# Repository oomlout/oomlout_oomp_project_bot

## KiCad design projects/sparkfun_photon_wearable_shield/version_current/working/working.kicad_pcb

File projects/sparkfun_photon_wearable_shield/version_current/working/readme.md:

# OOMP Project  
## Photon_Wearable_Shield  by sparkfun  
  
oomp key: oomp_projects_flat_sparkfun_photon_wearable_shield  
(snippet of original readme)  
  
SparkFun Photon Wearable Shield  
  
========================================  

[*SparkFun Photon Wearable Shield (DEV-13328)*](https://www.sparkfun.com/products/13328)  
  
The SparkFun Photon Wearable Shield makes it easy to add the WiFi enabled Photon to any wearables project. Each pin on the Photon is broken out into large sewing pins. Use conductive thread to make your next wearables projects. The large pins are also great for using conductive paint to create any project that needs WiFi. There are even optional smaller pins for soldering flexible wires. The SparkFun Photon Wearable Shield comes with the headers already soldered on, so you can plug and play!  
  
The Particle Photon is a tiny WiFi development kit for creating connected projects and products. Sporting a 120Mhz ARM Cortex M3 and built-in WiFi, the Photon is not only powerful, but easy to use. The small form factor is ideal for IoT projects with cloud-connectivity.  
  
Note: This Photon Wearable Shield does not include a Photon module and is currently available for preorder with a tentative release date of June 2015.  
  
Features:  
  
* 24 Large Sewing Tabs  
* Headers and Connectors Pre-Soldered  
* Compatible with the Photon and the Core  
  
Repository Contents  
-------------------  
  
* **/Production** - Production panel files (.brd)  
* **/Hardware** - Eagle design files (.brd, .sch)  
  
Documentation  
--------------  
* **[SparkFun Photon Wearab  
  full source readme at [readme_src.md](readme_src.md)  
  
source repo at: [https://github.com/sparkfun/Photon_Wearable_Shield](https://github.com/sparkfun/Photon_Wearable_Shield)  
## Board  

## Schematic  

[schematic pdf](working_schematic.pdf)  
## Images

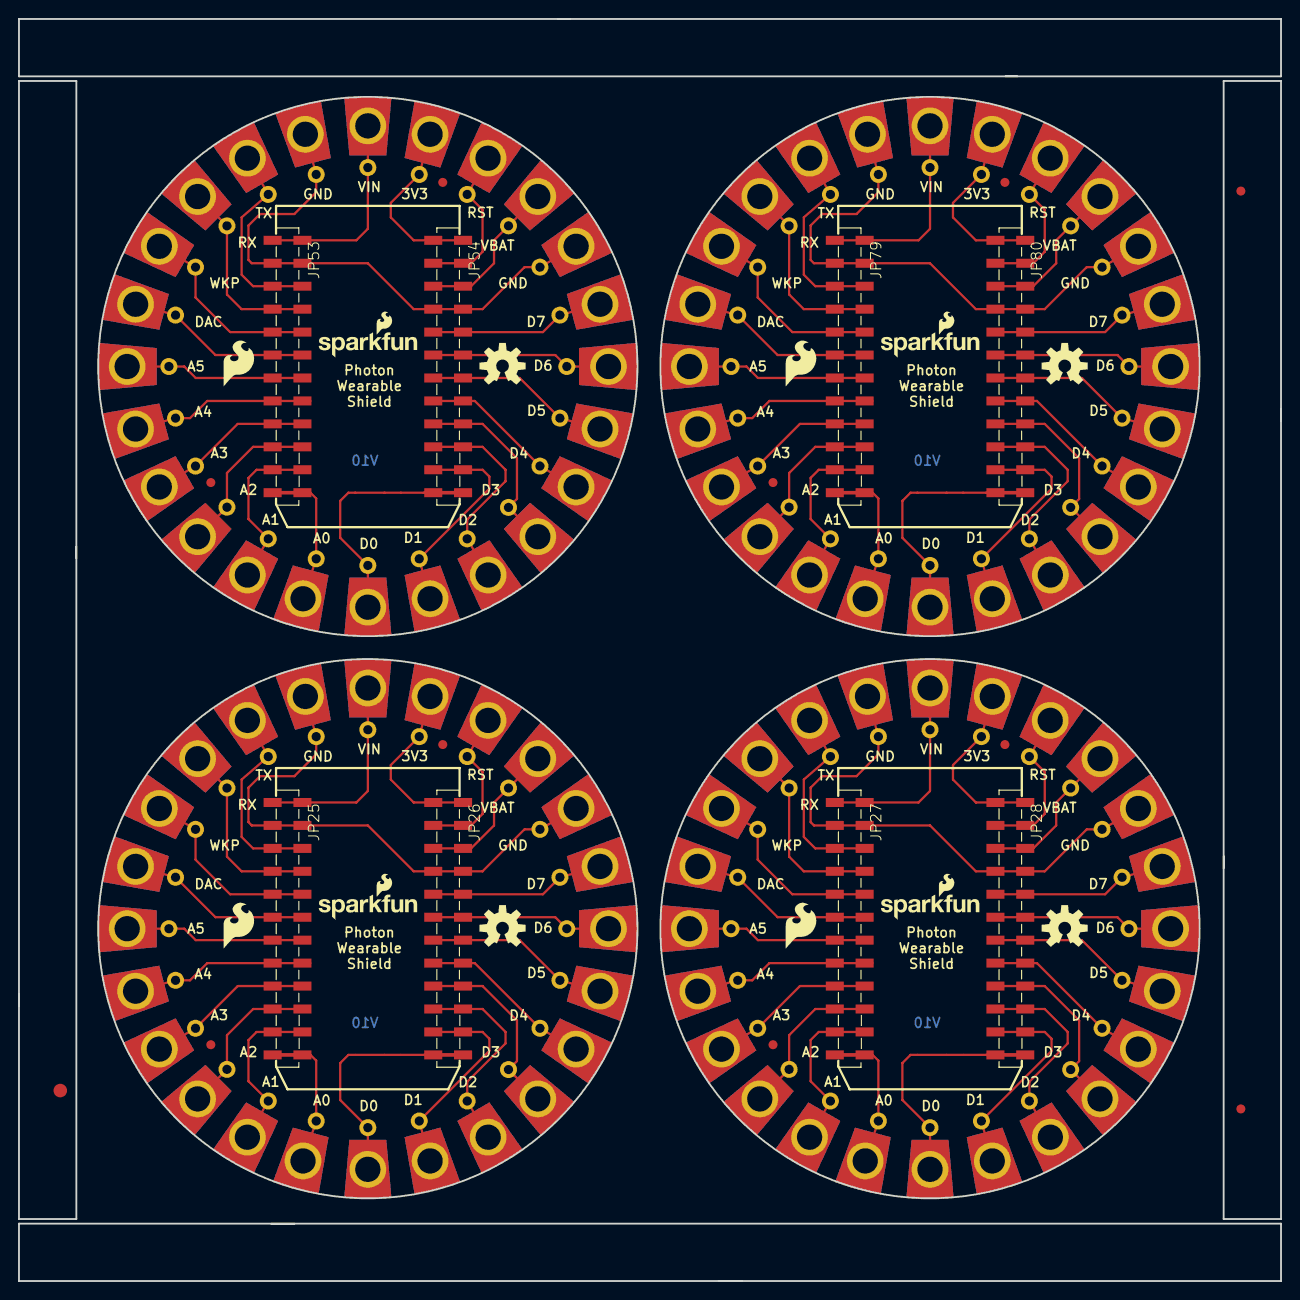
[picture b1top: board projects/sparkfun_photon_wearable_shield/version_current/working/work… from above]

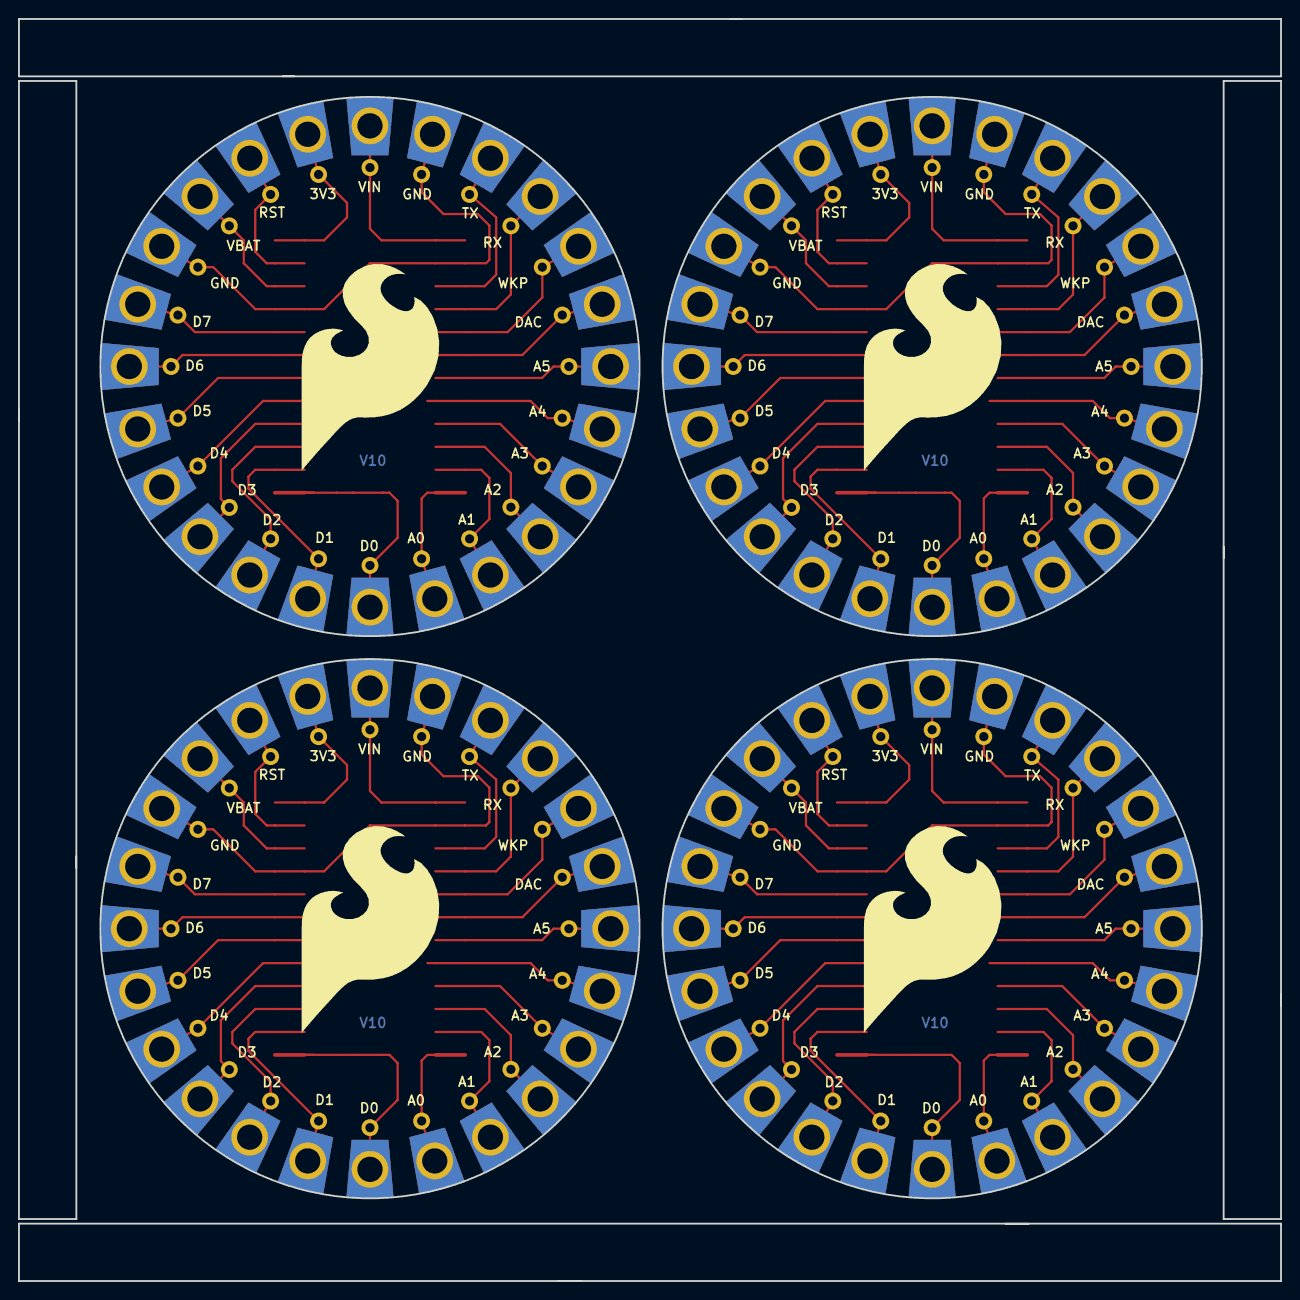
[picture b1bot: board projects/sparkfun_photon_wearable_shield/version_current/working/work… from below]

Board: 2 copper layers, 139.7 x 139.7 mm, 227 parts (4 on the bottom side), 92 nets.

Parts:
E$1: FIDUCIAL-1.5X3
E$4, E$5: FIDUCIAL-1X2
FID1, FID2, FID3, FID4, FID5, FID6, FID7, FID8: FIDUCIAL1X2; FIDUCIAL-1X2
J1, J2, J3, J4, J5, J6, J7, J8, J9, J10, J11, J12, J13, J14, J15, J16, J17, J18, J19, J20, J21, J22, J23, J24, J25, J26, J27, J28, J29, J30, J31, J32, J33, J34, J35, J36, J37, J38, J39, J40, J41, J42, J43, J44, J45, J46, J47, J48, J49, J50, J51, J52, J53, J54, J55, J56, J57, J58, J59, J60, J61, J62, J63, J64, J65, J66, J67, J68, J69, J70, J71, J72, J73, J74, J75, J76, J77, J78, J79, J80, J81, J82, J83, J84, J85, J86, J87, J88, J89, J90, J91, J92, J93, J94, J95, J96: PAD; PAD-LONG-2-SIDED
JP1, JP2, JP3, JP4, JP5, JP6, JP7, JP8, JP9, JP10, JP11, JP12, JP13, JP14, JP15, JP16, JP17, JP18, JP19, JP20, JP21, JP22, JP23, JP24, JP29, JP30, JP31, JP32, JP33, JP34, JP35, JP36, JP37, JP38, JP39, JP40, JP41, JP42, JP43, JP44, JP45, JP46, JP47, JP48, JP49, JP50, JP51, JP52, JP55, JP56, JP57, JP58, JP59, JP60, JP61, JP62, JP63, JP64, JP65, JP66, JP67, JP68, JP69, JP70, JP71, JP72, JP73, JP74, JP75, JP76, JP77, JP78, JP81, JP82, JP83, JP84, JP85, JP86, JP87, JP88, JP89, JP90, JP91, JP92, JP93, JP94, JP95, JP96, JP97, JP98, JP99, JP100, JP101, JP102, JP103, JP104: M01SMDNS; 1X01NS
JP25, JP26, JP27, JP28, JP53, JP54, JP79, JP80: M12SMD_COMBINED; 1X12_SMD_COMBINED
LOGO1, LOGO4, LOGO7, LOGO10: SFE_LOGO_FLAME.2_INCH; SFE_LOGO_FLAME_.2
LOGO2, LOGO5, LOGO8, LOGO11: OSHW-LOGOM; OSHW-LOGO-M
LOGO3, LOGO6, LOGO9, LOGO12: SFE_LOGO_NAME_FLAME.1_INCH; SFE_LOGO_NAME_FLAME_.1
U$1, U$2, U$3, U$4: SFE_LOGO_FLAME_.9

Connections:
3V1: J48.1, JP28.1A, JP28.1B, JP52.1
3V2: J72.1, JP54.1A, JP54.1B, JP78.1
3V3: J13.1, JP13.1, JP26.1A, JP26.1B
3V4: J96.1, JP80.1A, JP80.1B, JP104.1
A0: J12.1, JP12.1, JP25.12A, JP25.12B
A1: J11.1, JP11.1, JP25.11A, JP25.11B
A2: J10.1, JP10.1, JP25.10A, JP25.10B
A3: J9.1, JP9.1, JP25.9A, JP25.9B
A4: J8.1, JP8.1, JP25.8A, JP25.8B
A5: J7.1, JP7.1, JP25.7A, JP25.7B
A6: J31.1, JP27.7A, JP27.7B, JP35.1
A7: J32.1, JP27.8A, JP27.8B, JP36.1
A8: J33.1, JP27.9A, JP27.9B, JP37.1
A9: J34.1, JP27.10A, JP27.10B, JP38.1
A10: J35.1, JP27.11A, JP27.11B, JP39.1
A11: J36.1, JP27.12A, JP27.12B, JP40.1
A12: J55.1, JP53.7A, JP53.7B, JP61.1
A13: J56.1, JP53.8A, JP53.8B, JP62.1
A14: J57.1, JP53.9A, JP53.9B, JP63.1
A15: J58.1, JP53.10A, JP53.10B, JP64.1
A16: J59.1, JP53.11A, JP53.11B, JP65.1
A17: J60.1, JP53.12A, JP53.12B, JP66.1
A18: J79.1, JP79.7A, JP79.7B, JP87.1
A19: J80.1, JP79.8A, JP79.8B, JP88.1
A20: J81.1, JP79.9A, JP79.9B, JP89.1
A21: J82.1, JP79.10A, JP79.10B, JP90.1
A22: J83.1, JP79.11A, JP79.11B, JP91.1
A23: J84.1, JP79.12A, JP79.12B, JP92.1
D0: J24.1, JP24.1, JP26.12A, JP26.12B
D1: J23.1, JP23.1, JP26.11A, JP26.11B
D2: J22.1, JP22.1, JP26.10A, JP26.10B
D3: J21.1, JP21.1, JP26.9A, JP26.9B
D4: J20.1, JP20.1, JP26.8A, JP26.8B
D5: J19.1, JP19.1, JP26.7A, JP26.7B
D6: J18.1, JP18.1, JP26.6A, JP26.6B
D7: J17.1, JP17.1, JP26.5A, JP26.5B
D8: J44.1, JP28.5A, JP28.5B, JP48.1
D9: J43.1, JP28.6A, JP28.6B, JP47.1
D10: J42.1, JP28.7A, JP28.7B, JP46.1
D11: J41.1, JP28.8A, JP28.8B, JP45.1
D12: J40.1, JP28.9A, JP28.9B, JP44.1
D13: J39.1, JP28.10A, JP28.10B, JP43.1
D14: J38.1, JP28.11A, JP28.11B, JP42.1
D15: J37.1, JP28.12A, JP28.12B, JP41.1
D16: J68.1, JP54.5A, JP54.5B, JP74.1
D17: J67.1, JP54.6A, JP54.6B, JP73.1
D18: J66.1, JP54.7A, JP54.7B, JP72.1
D19: J65.1, JP54.8A, JP54.8B, JP71.1
D20: J64.1, JP54.9A, JP54.9B, JP70.1
D21: J63.1, JP54.10A, JP54.10B, JP69.1
D22: J62.1, JP54.11A, JP54.11B, JP68.1
D23: J61.1, JP54.12A, JP54.12B, JP67.1
D24: J92.1, JP80.5A, JP80.5B, JP100.1
D25: J91.1, JP80.6A, JP80.6B, JP99.1
D26: J90.1, JP80.7A, JP80.7B, JP98.1
D27: J89.1, JP80.8A, JP80.8B, JP97.1
D28: J88.1, JP80.9A, JP80.9B, JP96.1
D29: J87.1, JP80.10A, JP80.10B, JP95.1
D30: J86.1, JP80.11A, JP80.11B, JP94.1
D31: J85.1, JP80.12A, JP80.12B, JP93.1
DAC: J6.1, JP6.1, JP25.6A, JP25.6B
DAC1: J30.1, JP27.6A, JP27.6B, JP34.1
DAC2: J54.1, JP53.6A, JP53.6B, JP60.1
DAC3: J78.1, JP79.6A, JP79.6B, JP86.1
GND: J2.1, J16.1, JP2.1, JP16.1, JP25.2A, JP25.2B, JP26.4A, JP26.4B
GND1: J26.1, J45.1, JP27.2A, JP27.2B, JP28.4A, JP28.4B, JP31.1, JP49.1
GND2: J50.1, J69.1, JP53.2A, JP53.2B, JP54.4A, JP54.4B, JP57.1, JP75.1
GND3: J74.1, J93.1, JP79.2A, JP79.2B, JP80.4A, JP80.4B, JP83.1, JP101.1
RST: J14.1, JP14.1, JP26.2A, JP26.2B
RST1: J47.1, JP28.2A, JP28.2B, JP51.1
RST2: J71.1, JP54.2A, JP54.2B, JP77.1
RST3: J95.1, JP80.2A, JP80.2B, JP103.1
RX: J4.1, JP4.1, JP25.4A, JP25.4B
RX1: J28.1, JP27.4A, JP27.4B, JP32.1
RX2: J52.1, JP53.4A, JP53.4B, JP58.1
RX3: J76.1, JP79.4A, JP79.4B, JP84.1
TX: J3.1, JP3.1, JP25.3A, JP25.3B
TX1: J27.1, JP27.3A, JP27.3B, JP30.1
TX2: J51.1, JP53.3A, JP53.3B, JP56.1
TX3: J75.1, JP79.3A, JP79.3B, JP82.1
VBAT: J15.1, JP15.1, JP26.3A, JP26.3B
VBAT1: J46.1, JP28.3A, JP28.3B, JP50.1
VBAT2: J70.1, JP54.3A, JP54.3B, JP76.1
VBAT3: J94.1, JP80.3A, JP80.3B, JP102.1
VIN: J1.1, JP1.1, JP25.1A, JP25.1B
VIN1: J25.1, JP27.1A, JP27.1B, JP29.1
VIN2: J49.1, JP53.1A, JP53.1B, JP55.1
VIN3: J73.1, JP79.1A, JP79.1B, JP81.1
WKP: J5.1, JP5.1, JP25.5A, JP25.5B
WKP1: J29.1, JP27.5A, JP27.5B, JP33.1
WKP2: J53.1, JP53.5A, JP53.5B, JP59.1
WKP3: J77.1, JP79.5A, JP79.5B, JP85.1

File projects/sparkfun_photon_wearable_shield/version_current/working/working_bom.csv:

Row,Description,Part,References,Value,Footprint,Quantity Per PCB,Status,Datasheet
1,,FRAME-LETTER,FRAME1,FRAME-LETTER,CREATIVE_COMMONS,1, ,
2,,PAD,J1 J2 J3 J4 J5 J6 J7 J8 J9 J10 J11 J12 J13 J14 J15 J16 J17 J18 J19 J20 J21 J22 J23 J24,PAD,PAD-LONG-2-SIDED,24, ,
3,,M01SMDNS,JP1 JP2 JP3 JP4 JP5 JP6 JP7 JP8 JP9 JP10 JP11 JP12 JP13 JP14 JP15 JP16 JP17 JP18 JP19 JP20 JP21 JP22 JP23 JP24,M01SMDNS,1X01NS,24, ,
4,,M12SMD_COMBINED,JP25 JP26,M12SMD_COMBINED,1X12_SMD_COMBINED,2, ,
5,,OSHW-LOGOM,LOGO2,OSHW-LOGOM,OSHW-LOGO-M,1, ,
6,,SFE_LOGO_FLAME.2_INCH,LOGO1,SFE_LOGO_FLAME.2_INCH,SFE_LOGO_FLAME_.2,1, ,
7,,SFE_LOGO_NAME_FLAME.1_INCH,LOGO3,SFE_LOGO_NAME_FLAME.1_INCH,SFE_LOGO_NAME_FLAME_.1,1, ,





Project info:
Schematic:,working
Variant:,default
Revision:,
Date:,2023-08-06_12-56-12
KiCad Version:,7.0.6-7.0.6~ubuntu22.04.1
Statistics:
Component Groups:,7
Component Count:,54 (0 SMD/ 0 THT)
Fitted Components:,54 (0 SMD/ 0 THT)
Number of PCBs:,1
Total Components:,54

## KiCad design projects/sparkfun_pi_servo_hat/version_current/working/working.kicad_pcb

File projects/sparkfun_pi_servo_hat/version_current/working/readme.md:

# OOMP Project  
## Pi_Servo_Hat  by sparkfun  
  
oomp key: oomp_projects_flat_sparkfun_pi_servo_hat  
(snippet of original readme)  
  
SparkFun Pi Servo pHAT  
=====================  

[SparkFun Servo pHAT for Raspberry Pi (DEV-15316)](https://www.sparkfun.com/products/15316)  
  
<!--  
<table class="table table-hover table-striped table-bordered">  
  <tr align="center">  
   <td></td>  
   <td></td>  
  </tr>  
  <tr align="center">  
    <td><i>Pi Servo Hat [<a href="https://www.sparkfun.com/products/14328">DEV-14328</a>]</i></td>  
    <td><i>SparkFun Raspberry Pi Zero W Camera Kit [<a href="https://www.sparkfun.com/products/14329">KIT-14329</a>]</i></td>  
  </tr>  
</table>  
-->  
  
The Pi Servo pHAT is a hat that adds, via I<sup>2</sup>C, the ability to control up to 16 servo motors with a Raspberry Pi. It is the same size and form factor as a Pi Zero or Pi Zero W. The Pi Servo pHAT is great for adding pan/tilt control with the Raspberry Pi Camera to create homemade motion-activated security systems, webcam interfaces for streaming, or monitoring stations for any number of pr  
  full source readme at [readme_src.md](readme_src.md)  
  
source repo at: [https://github.com/sparkfun/Pi_Servo_Hat](https://github.com/sparkfun/Pi_Servo_Hat)  
## Board  

## Schematic  

[schematic pdf](working_schematic.pdf)  
## Images

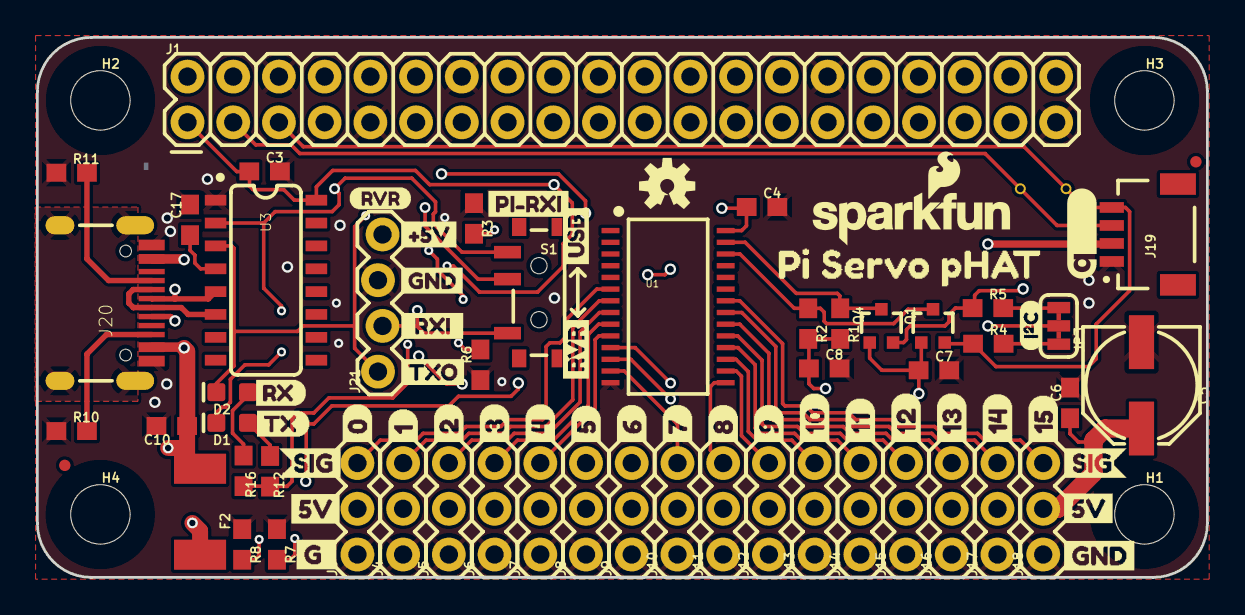
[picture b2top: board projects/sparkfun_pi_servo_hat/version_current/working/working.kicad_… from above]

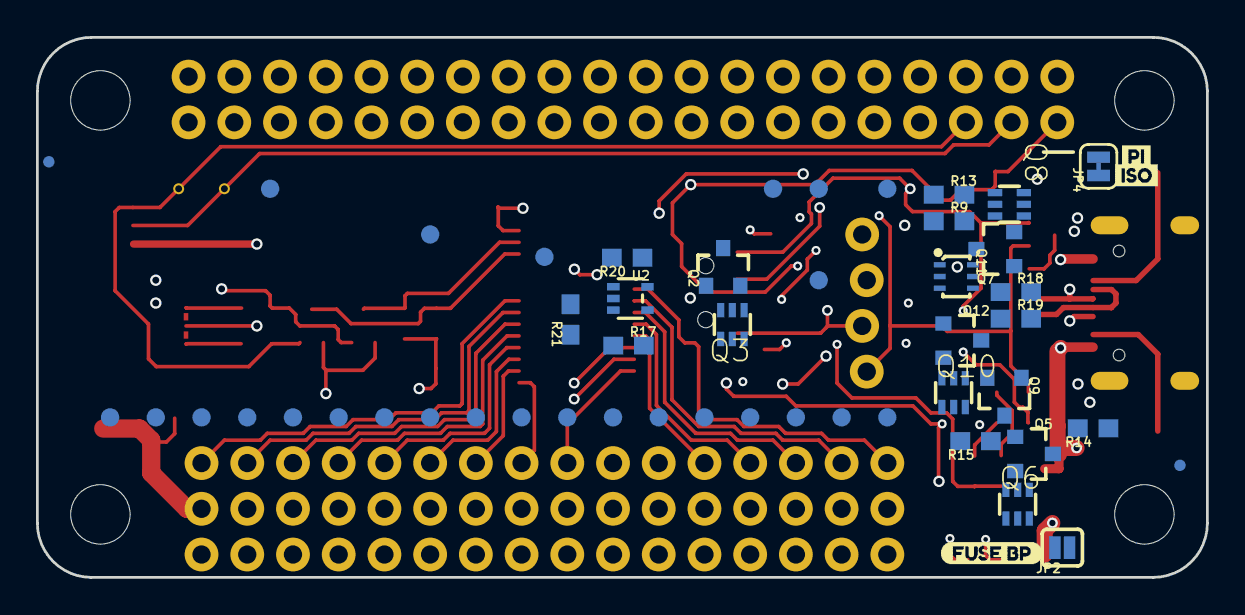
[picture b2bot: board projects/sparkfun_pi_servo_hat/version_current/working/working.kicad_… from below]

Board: 4 copper layers, 65.0 x 30.0 mm, 148 parts (52 on the bottom side), 54 nets.

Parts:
C3, C4, C6, C7, C8, C10: 0.1uF; 0603
C5: 100uF; PANASONIC_D
C17: 10nF; 0603
D1: GREEN; LED-0603
D2: Yellow; LED-0603
F2: 16V/2.5A(5A TRIP); 1812
FD1, FD2, FD3, FD4: FIDUCIALUFIDUCIAL; FIDUCIAL-MICRO
FRAME2: FRAME-LEDGER; CREATIVE_COMMONS
H1, H2, H3, H4: STAND-OFF
J1: RASPBERRYPI-40-PIN-GPIO; 2X20
J3, J4, J5, J6, J7, J8, J9, J10, J11, J12, J13, J14, J15, J16, J17, J18: 1X03
J19: QWIIC; JST04_1MM_RA
J20: USB C; USB-C-16P
J21: RVR; 1X04_LOCK
JP2: FUSE BP; SMT-JUMPER_2_NO_SILK
JP3: I2C; SMT-JUMPER_3_2-NC_TRACE_SILK
JP4: PI ISO; SMT-JUMPER_2_NC_TRACE_SILK
LOGO1: SFE_LOGO_NAME_FLAME.1_INCH; SFE_LOGO_NAME_FLAME_.1
LOGO2: OSHW-LOGOS; OSHW-LOGO-S
Q1, Q4: 310mA/60V/1.6Ω; SOT323
Q2, Q5, Q7, Q9, Q12: 20V/4.2A/52mΩ/1.4W; SOT23-3
Q3, Q6, Q8, Q10: SOT363_PHILIPS
Q11: SC70-6
R1, R2, R4, R5, R6, R8, R13, R15, R19, R20, R21: 10k; 0603
R3, R7, R9, R14: 47k; 0603
R10, R11: 5.1k; 0603
R12: 330; 0603
R16: 1k; 0603
R17, R18: 240; 0603
S1: SWITCH_SPST_SMD_A
TP0, TP1, TP2, TP3, TP4, TP5, TP6, TP7, TP8, TP9, TP10, TP11, TP12, TP13, TP14, TP15, TP16, TP17, TP20, TP21, TP22, TP23, TP24, TP25, TP26: PAD.03X.04
TP18, TP19: TP_15TH
U1: PCA9685; TSSOP-28_4MM
U2: SN74LVC1G32DCKR; SOT353
U3: CH340C; SO016
U$1: QWIIC_LOGO_5MM; QWIIC_5MM
U$2: I_SUPER2_C-()-03
U$3: 028
U$4: 129
U$5: 230
U$6: 331
U$7: 432
U$8: 533
U$9: 634
U$10: 735
U$11: 836
U$12: 937
U$13: 1038
U$14: 1139
U$15: 1240
U$16: 1341
U$17: 1442
U$18: 1543
U$20, U$24: 5V5
U$21: SIG2
U$22: SIG3
U$23: GND25
U$25: TXO0
U$26: PI#RXI2
U$27: #5V3
U$28: GND2
U$30: RASP_μPI_HAT_SPECIFICATION
U$31: RVR1
U$32: ISO1
U$33: _RXI_0
U$34: USB0
U$35: PI0
U$36: RX0
U$37: TX1
U$38: RVR0
U$39: FUSE_BP0
U$40: G_0
U$41: PI_SERVO_PHAT0

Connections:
3.3V: C3.1, C7.1, J1.1, J1.17, J19.2, JP3.2, Q1.1, Q4.1, R12.2, R16.2, TP22.P$1, U3.16
CC1: J20.A5, R11.2
CC2: J20.B5, R10.2
CH0: J3.3, TP0.P$1, U1.6
CH1: J4.3, TP1.P$1, U1.7
CH2: J5.3, TP2.P$1, U1.8
CH3: J6.3, TP3.P$1, U1.9
CH4: J7.3, TP4.P$1, U1.10
CH5: J8.3, TP5.P$1, U1.11
CH6: J9.3, TP6.P$1, U1.12
CH7: J10.3, TP7.P$1, U1.13
CH8: J11.3, TP8.P$1, U1.15
CH9: J12.3, TP9.P$1, U1.16
CH10: J13.3, TP10.P$1, U1.17
CH11: J14.3, TP11.P$1, U1.18
CH12: J15.3, TP12.P$1, U1.19
CH13: J16.3, TP13.P$1, U1.20
CH14: J17.3, TP14.P$1, U1.21
CH15: J18.3, TP15.P$1, U1.22
CH340-TXO: D1.C, S1.1, TP23.P$1, U3.2
D+: J20.A6, J20.B6, U3.5
D-: J20.A7, J20.B7, U3.6
GND: C3.2, C4.2, C5.-, C6.2, C7.2, C8.2, C10.2, C17.2, J1.6, J1.9, J1.14, J1.20, J1.25, J1.30, J1.34, J1.39, J3.1, J4.1, J5.1, J6.1, J7.1, J8.1, J9.1, J10.1, J11.1, J12.1, J13.1, J14.1, J15.1, J16.1, J17.1, J18.1, J19.1, J20.GND, J20.GND2, J21.3, Q11.1, Q11.4, R3.1, R6.1, R7.1, R8.1, R9.1, R10.1, R11.1, R13.1, R14.1, R15.1, R20.1, R21.1, TP17.P$1, U1.14, U1.23, U1.25, U2.3, U3.1
LV_SCL: J1.5, J19.4, Q1.2, R4.1, TP18.P$1
LV_SDA: J1.3, J19.3, Q4.2, R5.1, TP19.P$1
unnamed: Q5.1, Q6.3, R7.2
unnamed: JP3.3, R4.2
unnamed: Q1.3, R2.1, U1.26
unnamed: Q4.3, R1.1, U1.27
unnamed: JP3.1, R5.2
unnamed: D2.A, R16.1
unnamed: D1.A, R12.1
unnamed: Q11.2, R17.2
unnamed: Q2.1, Q3.3, R3.2
unnamed: Q3.2, Q3.5, Q3.6, R6.2
unnamed: Q6.2, Q6.5, Q6.6, R8.2
unnamed: Q11.5, Q11.6, R18.1
unnamed: Q11.3, Q12.1, R19.1
unnamed: C17.1, U3.4
unnamed: Q7.1, Q8.3, R9.2
unnamed: Q8.2, Q8.5, Q8.6, R13.2
unnamed: R17.1, U2.4
unnamed: Q9.1, Q10.3, R14.2
unnamed: Q10.2, Q10.5, Q10.6, R15.2
unnamed: J1.2, JP4.2
PI-5V: C4.1, C8.1, JP4.1, Q7.2, Q8.4, Q9.2, Q10.4, Q12.3, R1.2, R2.2, R18.2, R19.2, TP24.P$1, U1.28, U2.5
PI-RXI: J1.10, S1.2, TP26.P$1
PI-TXO: D2.C, J1.8, J21.1, TP20.P$1, U3.3
RVR-5V: J21.4, Q2.3, Q3.1, Q7.3, Q8.1, R20.2, TP25.P$1, U2.1
RVR-TXO: J21.2, S1.3, TP21.P$1
SERVO: C5.+, C6.1, J3.2, J4.2, J5.2, J6.2, J7.2, J8.2, J9.2, J10.2, J11.2, J12.2, J13.2, J14.2, J15.2, J16.2, J17.2, J18.2, Q2.2, Q3.4, Q5.2, Q6.4, Q12.2, TP16.P$1
SHLD: J20.SHLD1, J20.SHLD2, J20.SHLD3, J20.SHLD4, J20.SHLD5, J20.SHLD6, J20.SHLD7, J20.SHLD8
USB-5V: F2.2, JP2.2, Q5.3, Q6.1, Q9.3, Q10.1, R21.2, U2.2
VBUS: C10.1, F2.1, J20.VBUS1, J20.VBUS2, JP2.1

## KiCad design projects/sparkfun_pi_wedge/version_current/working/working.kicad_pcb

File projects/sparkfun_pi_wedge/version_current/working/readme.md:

# Pi_Wedge by sparkfun  
This is a harvested standardized copy of a project from github.  
The original project can be found at:  
https://github.com/sparkfun/Pi_Wedge  
Please consult that link for additional, details, files, and license information.  
Note: It was auto harvested and if the original repo had more than one board file or anything out of the ordinary the files here are likely not representative.

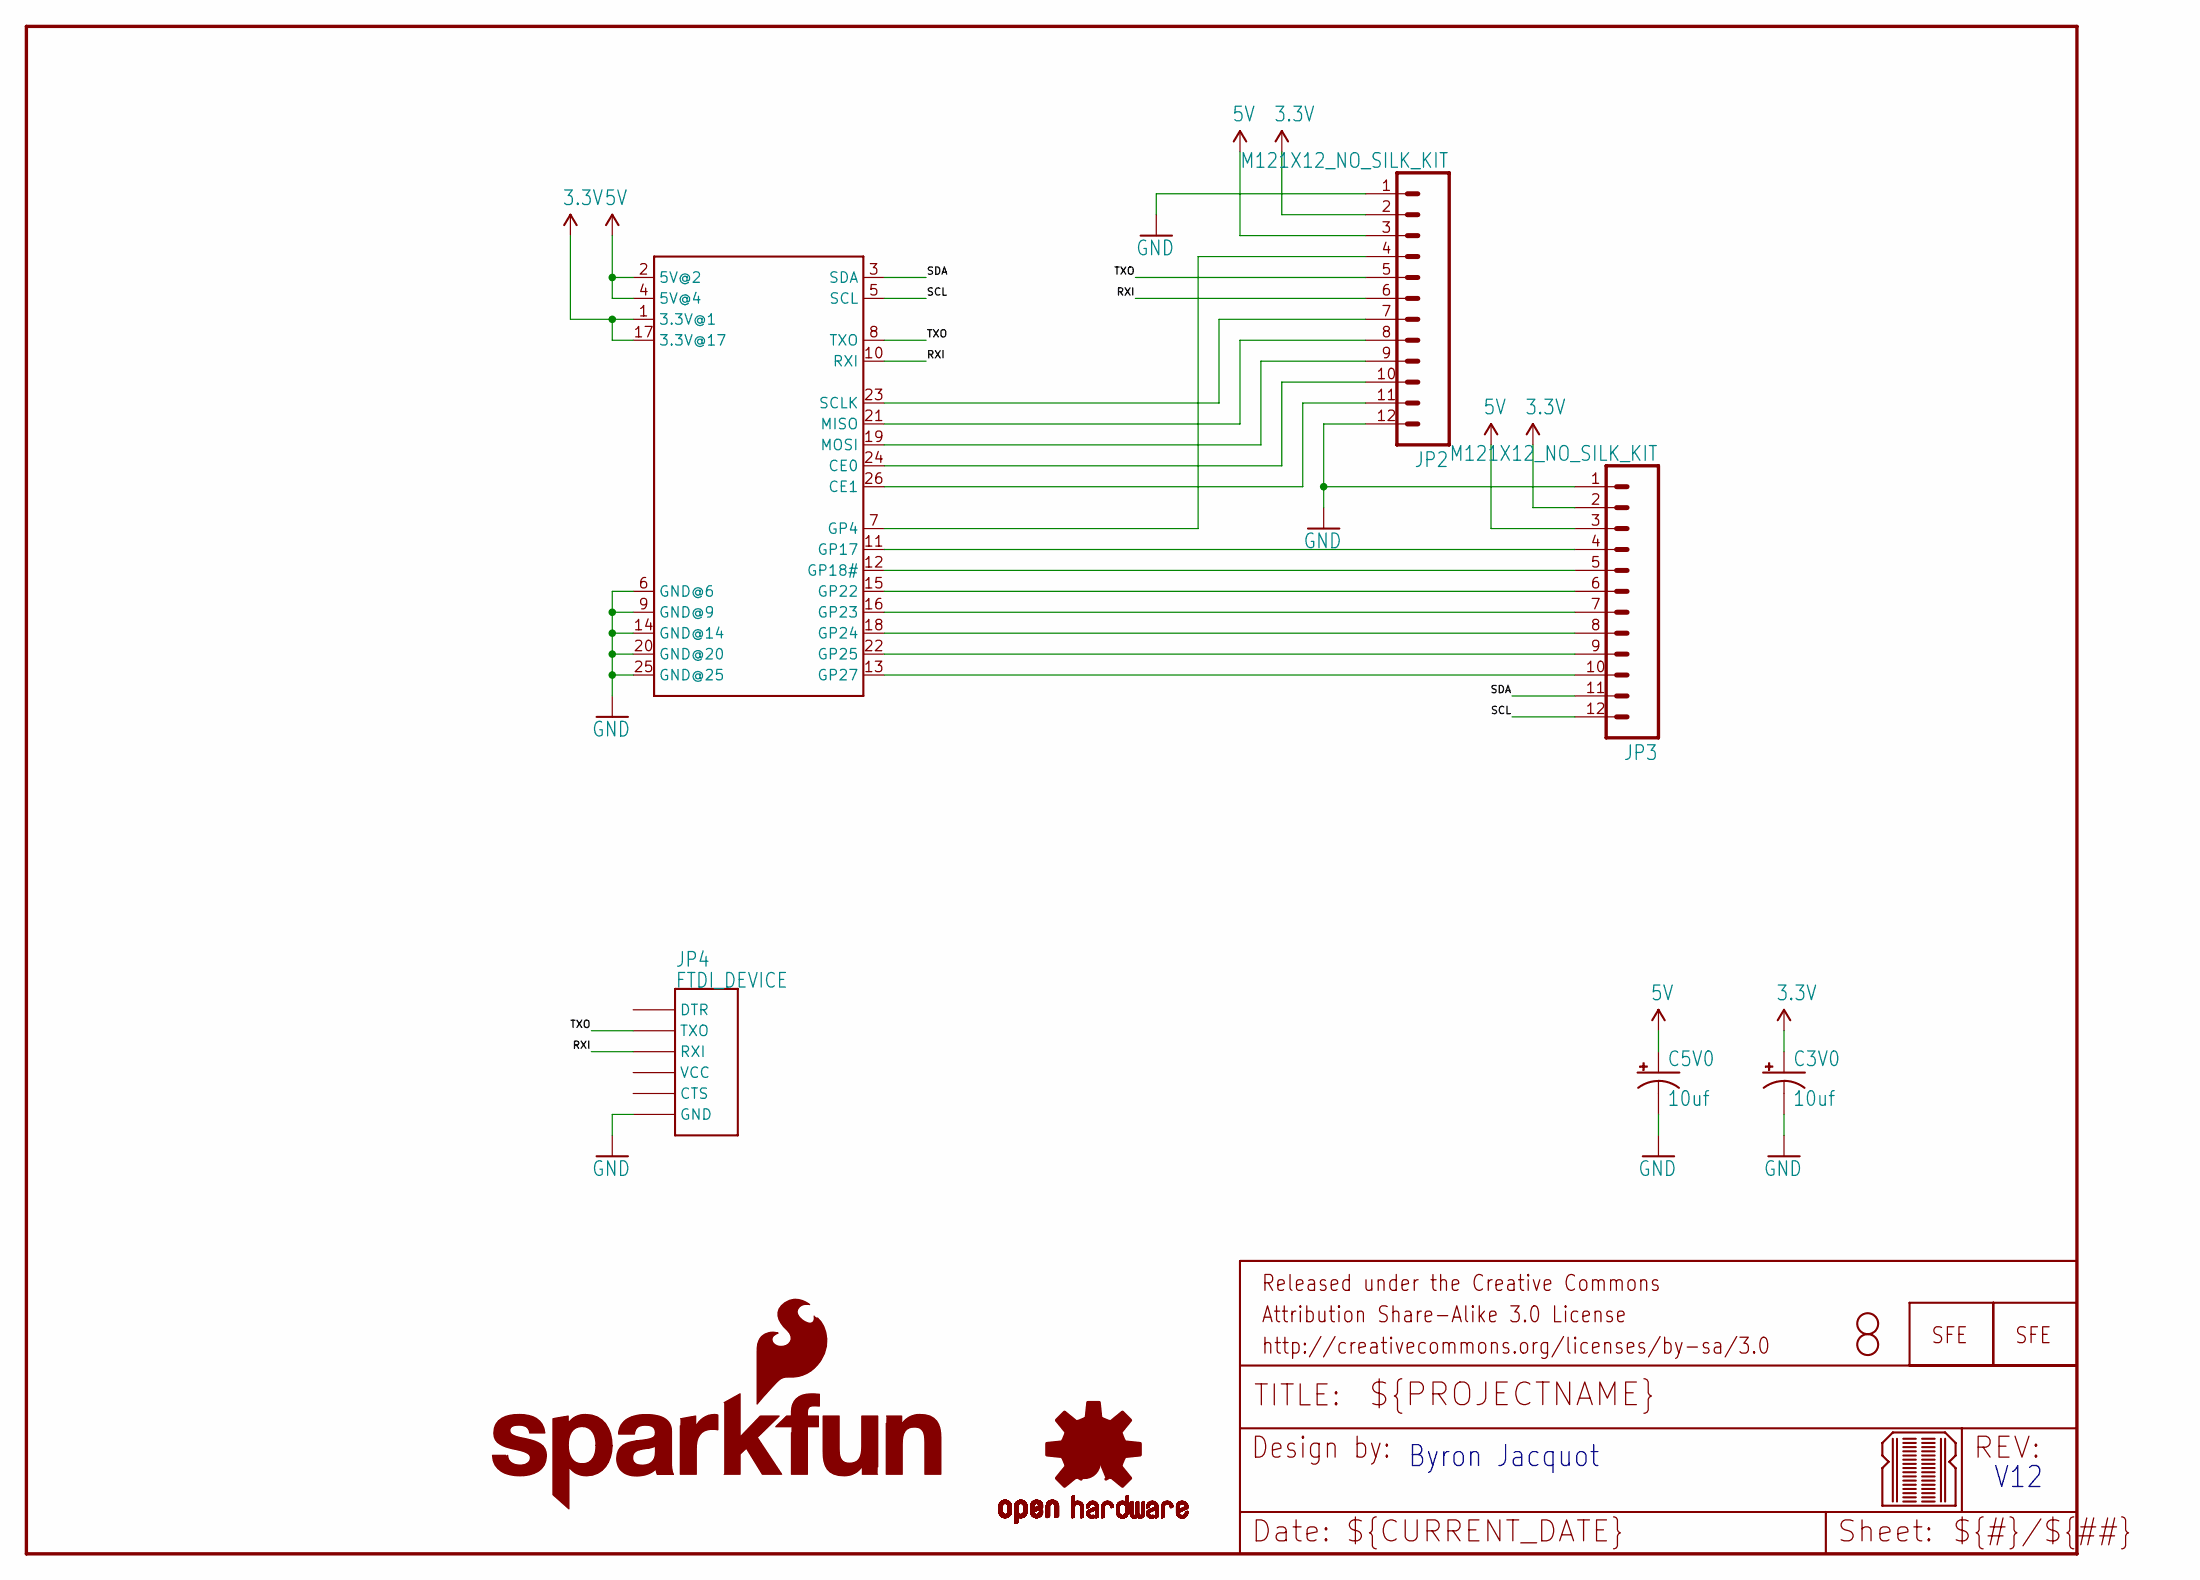
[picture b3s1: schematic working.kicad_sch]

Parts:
C3V0, C5V0: 10uf; CPOL-RADIAL-10UF-25V-KIT
FRAME2: FRAME-LETTER; CREATIVE_COMMONS
JP1, JP5: LOGO-SFESK; SFE-LOGO-FLAME
JP2, JP3: M121X12_NO_SILK_KIT; 1X12_NO_SILK_KIT
JP4: FTDI_DEVICE; FTDI_DEVICE_SIDE
JP8: RASPBERRYPI-GPIOPTH; 2X13-SHROUDED
LOGO1: SFE_LOGO_NAME_FLAME.2_INCH; SFE_LOGO_NAME_FLAME_.2
STANDOFF1, STANDOFF2: STAND-OFF
U$1: OSHW-LOGOS; OSHW-LOGO-S
U$2: BREADBOARD_PATTERN; BREADBOARD_SPACING

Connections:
3.3V: C3V0.1 (+), JP2.2, JP3.2, JP8.1 (3.3V@1), JP8.17 (3.3V@17)
5V: C5V0.1 (+), JP2.3, JP3.3, JP8.2 (5V@2), JP8.4 (5V@4)
CE0: JP2.10, JP8.24 (CE0)
CE1: JP2.11, JP8.26 (CE1)
GND: C3V0.2 (-), C5V0.2 (-), JP2.1, JP2.12, JP3.1, JP4.P$6 (GND), JP8.6 (GND@6), JP8.9 (GND@9), JP8.14 (GND@14), JP8.20 (GND@20), JP8.25 (GND@25)
GP4: JP2.4, JP8.7 (GP4)
GP17: JP3.4, JP8.11 (GP17)
GP18: JP3.5, JP8.12 (GP18#)
GP22: JP3.6, JP8.15 (GP22)
GP23: JP3.7, JP8.16 (GP23)
GP24: JP3.8, JP8.18 (GP24)
GP25: JP3.9, JP8.22 (GP25)
GP27: JP3.10, JP8.13 (GP27)
MISO: JP2.8, JP8.21 (MISO)
MOSI: JP2.9, JP8.19 (MOSI)
RXI: JP2.6, JP4.P$3 (RXI), JP8.10 (RXI)
SCL: JP3.12, JP8.5 (SCL)
SCLK: JP2.7, JP8.23 (SCLK)
SDA: JP3.11, JP8.3 (SDA)
TXO: JP2.5, JP4.P$2 (TXO), JP8.8 (TXO)

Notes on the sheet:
Byron Jacquot
V12

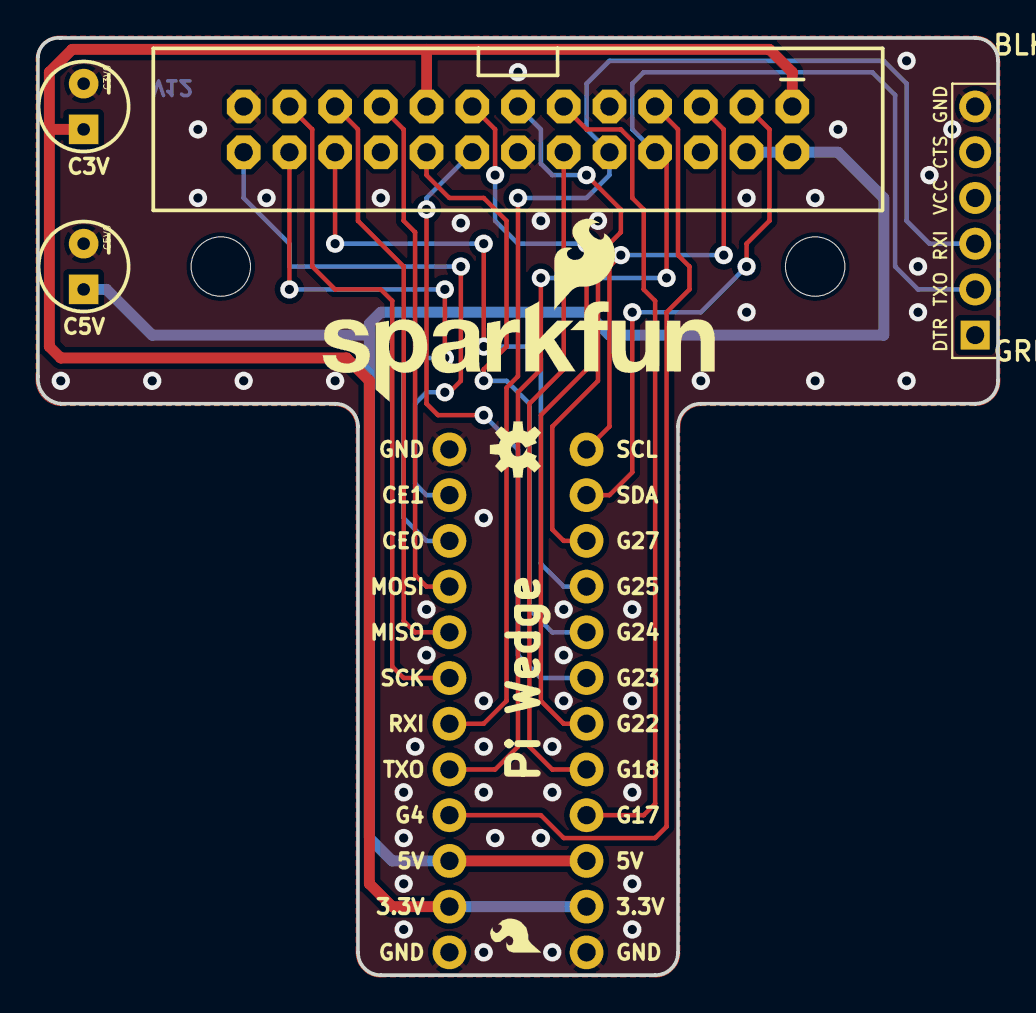
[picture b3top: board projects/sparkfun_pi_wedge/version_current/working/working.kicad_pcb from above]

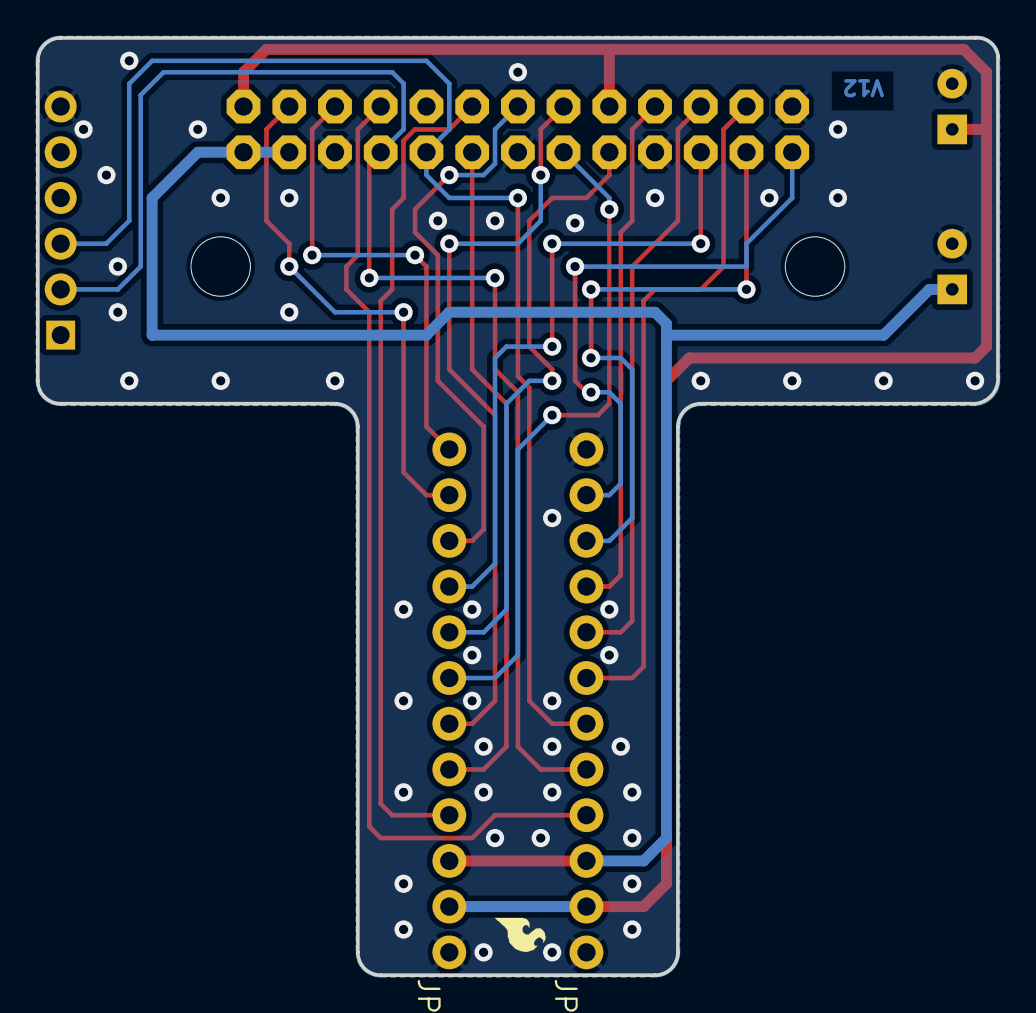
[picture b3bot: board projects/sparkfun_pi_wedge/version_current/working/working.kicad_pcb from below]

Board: 2 copper layers, 53.3 x 52.1 mm, 14 parts (3 on the bottom side), 20 nets.

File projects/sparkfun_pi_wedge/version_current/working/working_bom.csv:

Row,Description,Part,References,Value,Footprint,Quantity Per PCB,Status,Datasheet
1,,10UF-25V-20%(PTH)KIT,C3V0 C5V0,10uf,CPOL-RADIAL-10UF-25V-KIT,2, ,
2,,FRAME-LETTER,FRAME2,FRAME-LETTER,CREATIVE_COMMONS,1, ,
3,,FTDI_DEVICE,JP4,FTDI_DEVICE,FTDI_DEVICE_SIDE,1, ,
4,,LOGO-SFESK,JP1 JP5,LOGO-SFESK,SFE-LOGO-FLAME,2, ,
5,,M121X12_NO_SILK_KIT,JP2 JP3,M121X12_NO_SILK_KIT,1X12_NO_SILK_KIT,2, ,
6,,RASPBERRYPI-GPIOPTH,JP8,RASPBERRYPI-GPIOPTH,2X13-SHROUDED,1, ,
7,,SFE_LOGO_NAME_FLAME.2_INCH,LOGO1,SFE_LOGO_NAME_FLAME.2_INCH,SFE_LOGO_NAME_FLAME_.2,1, ,
8,,STAND-OFF,STANDOFF1 STANDOFF2,STAND-OFF,STAND-OFF,2, ,
9,,BREADBOARD_PATTERN,U$2,BREADBOARD_PATTERN,BREADBOARD_SPACING,1, ,
10,,OSHW-LOGOS,U$1,OSHW-LOGOS,OSHW-LOGO-S,1, ,





Project info:
Schematic:,working
Variant:,default
Revision:,
Date:,2023-08-06_12-56-12
KiCad Version:,7.0.6-7.0.6~ubuntu22.04.1
Statistics:
Component Groups:,10
Component Count:,14 (0 SMD/ 0 THT)
Fitted Components:,14 (0 SMD/ 0 THT)
Number of PCBs:,1
Total Components:,14

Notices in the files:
projects/sparkfun_photon_wearable_shield/version_current/working/working.kicad_sch:
Released under the Creative Commons
parts and their libraries:
Released under the Creative Commons Attribution Share-Alike 4.0 License
Released under the Creative Commons Attribution Share-Alike 3.0 License
